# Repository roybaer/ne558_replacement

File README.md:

# NE558 drop-in replacement

This is a drop-in replacement for the Texas Instruments NE558 quad timer IC based on two Texas Instruments NE556 dual timer ICs.
It is primarily intended for joystick interfaces and similar applications.  Other applications might need adjustments to the support circuitry.

The design has not been verified, yet.

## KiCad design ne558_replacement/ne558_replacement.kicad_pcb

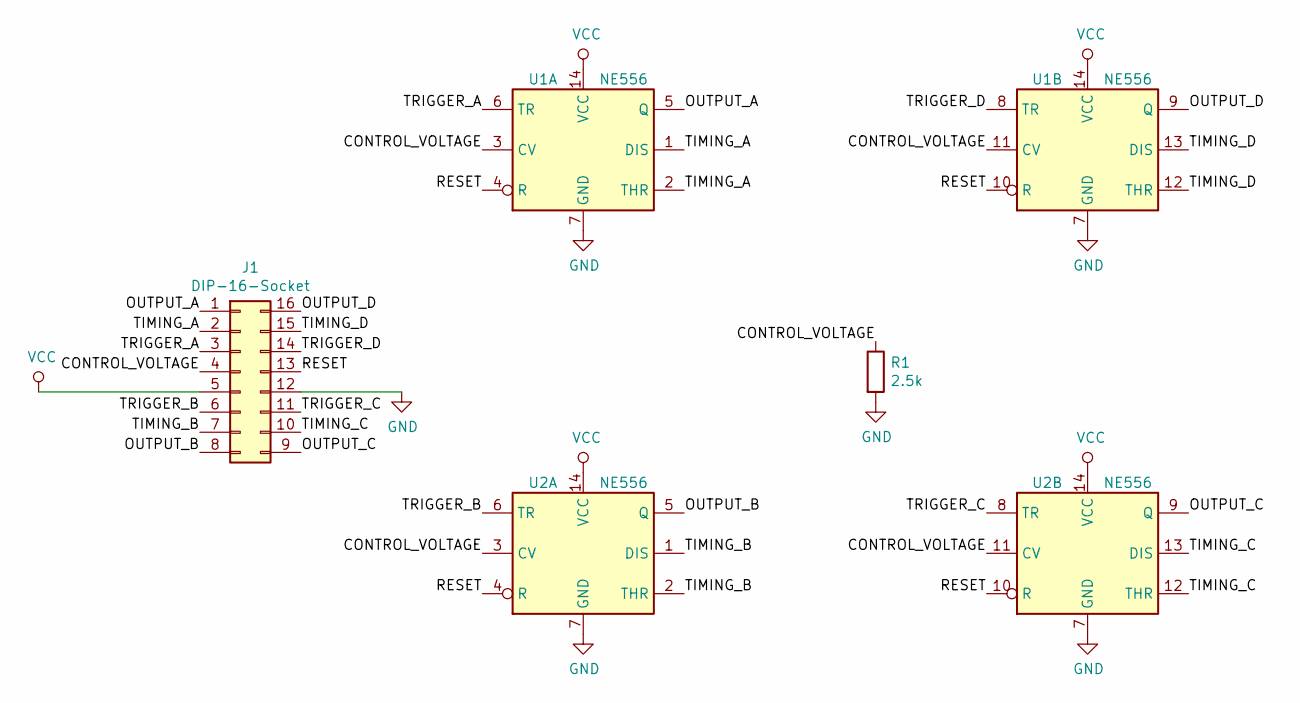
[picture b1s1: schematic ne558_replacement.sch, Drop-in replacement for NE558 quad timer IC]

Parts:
J1: DIP-16-Socket; DIP-16_W7.62mm_Socket
R1: 2.5k; R_0603_1608Metric
U1, U2: NE556; SSOP-14_5.3x6.2mm_P0.65mm

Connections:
/CONTROL_VOLTAGE: J1.4, R1.1, U1.3 (CV), U1.11 (CV), U2.3 (CV), U2.11 (CV)
/OUTPUT_A: J1.1, U1.5 (Q)
/OUTPUT_B: J1.8, U2.5 (Q)
/OUTPUT_C: J1.9, U2.9 (Q)
/OUTPUT_D: J1.16, U1.9 (Q)
/RESET: J1.13, U1.4 (R), U1.10 (R), U2.4 (R), U2.10 (R)
/TIMING_A: J1.2, U1.1 (DIS), U1.2 (THR)
/TIMING_B: J1.7, U2.1 (DIS), U2.2 (THR)
/TIMING_C: J1.10, U2.12 (THR), U2.13 (DIS)
/TIMING_D: J1.15, U1.12 (THR), U1.13 (DIS)
/TRIGGER_A: J1.3, U1.6 (TR)
/TRIGGER_B: J1.6, U2.6 (TR)
/TRIGGER_C: J1.11, U2.8 (TR)
/TRIGGER_D: J1.14, U1.8 (TR)
GND: J1.12, R1.2, U1.7 (GND), U2.7 (GND)
VCC: J1.5, U1.14 (VCC), U2.14 (VCC)

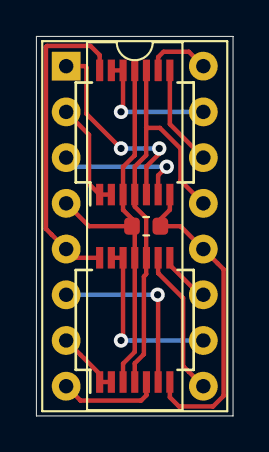
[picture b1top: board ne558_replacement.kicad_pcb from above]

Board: 2 copper layers, 10.9 x 21.1 mm, 4 parts (0 on the bottom side), 16 nets.

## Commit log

2019-10-19 add .gitignore and README.md
2024-03-19 Add production files
